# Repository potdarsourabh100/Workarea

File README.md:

# Workarea
My Own Personal Projects

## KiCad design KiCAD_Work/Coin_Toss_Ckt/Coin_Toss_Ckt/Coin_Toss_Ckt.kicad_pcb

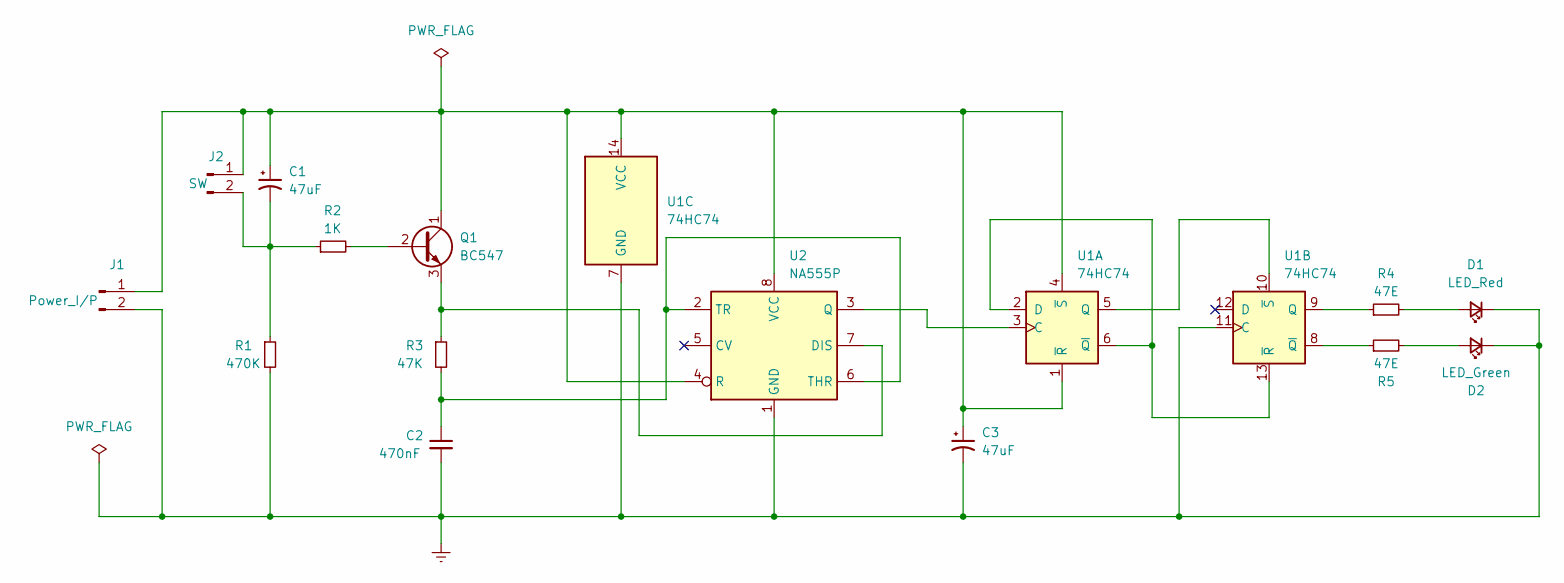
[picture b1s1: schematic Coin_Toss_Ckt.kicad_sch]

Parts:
C1, C3: 47uF; CP_Radial_D5.0mm_P2.50mm
C2: 470nF; CP_Radial_D5.0mm_P2.50mm
D1: LED_Red; LED_D3.0mm
D2: LED_Green; LED_D3.0mm
J1: Power_I/P; TerminalBlock_Phoenix_MPT-0,5-2-2.54_1x02_P2.54mm_Horizontal
J2: SW; PinHeader_1x02_P2.54mm_Vertical
Q1: BC547; TO-92_Inline
R1: 470K; R_Axial_DIN0207_L6.3mm_D2.5mm_P10.16mm_Horizontal
R2: 1K; R_Axial_DIN0207_L6.3mm_D2.5mm_P10.16mm_Horizontal
R3: 47K; R_Axial_DIN0207_L6.3mm_D2.5mm_P10.16mm_Horizontal
R4, R5: 47E; R_Axial_DIN0207_L6.3mm_D2.5mm_P10.16mm_Horizontal
U1: 74HC74; DIP-14_W7.62mm_Socket_LongPads
U2: NA555P; DIP-8_W7.62mm_Socket_LongPads

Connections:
Earth: C2.2, C3.2, D1.1 (K), D2.1 (K), J1.2, R1.2, U1.7 (GND), U1.11 (C), U2.1 (GND)
unnamed: C1.1, C3.1, J1.1, J2.1, Q1.1 (C), U1.1 (~R), U1.4 (~S), U1.14 (VCC), U2.4 (R), U2.8 (VCC)
unnamed: C1.2, J2.2, R1.1, R2.1
unnamed: C2.1, R3.2, U2.2 (TR), U2.6 (THR)
unnamed: D1.2 (A), R4.2
unnamed: D2.2 (A), R5.2
unnamed: Q1.2 (B), R2.2
unnamed: Q1.3 (E), R3.1, U2.7 (DIS)
unnamed: R4.1, U1.9 (Q)
unnamed: R5.1, U1.8 (~Q)
unnamed: U1.3 (C), U2.3 (Q)
unnamed: U1.5 (Q), U1.10 (~S)
unnamed: U1.2 (D), U1.6 (~Q), U1.13 (~R)

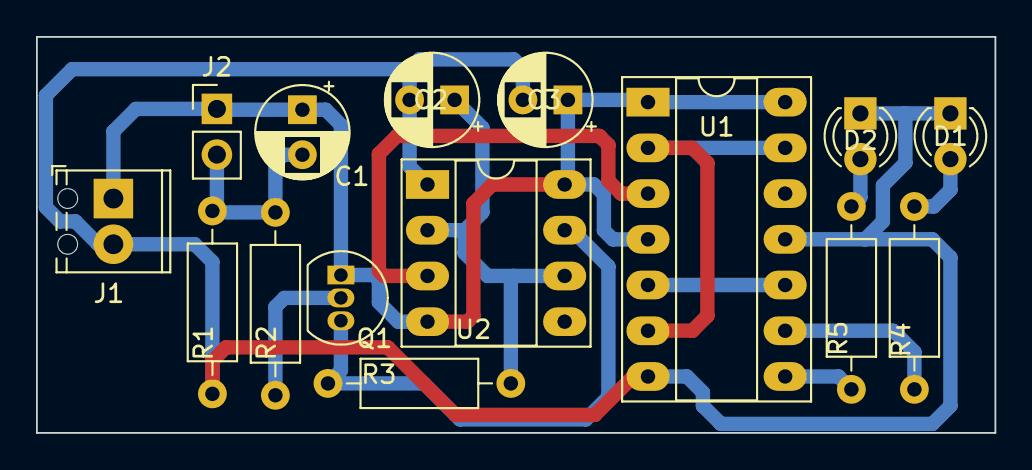
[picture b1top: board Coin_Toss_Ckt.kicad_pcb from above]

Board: 2 copper layers, 53.2 x 22.0 mm, 15 parts (0 on the bottom side), 13 nets.

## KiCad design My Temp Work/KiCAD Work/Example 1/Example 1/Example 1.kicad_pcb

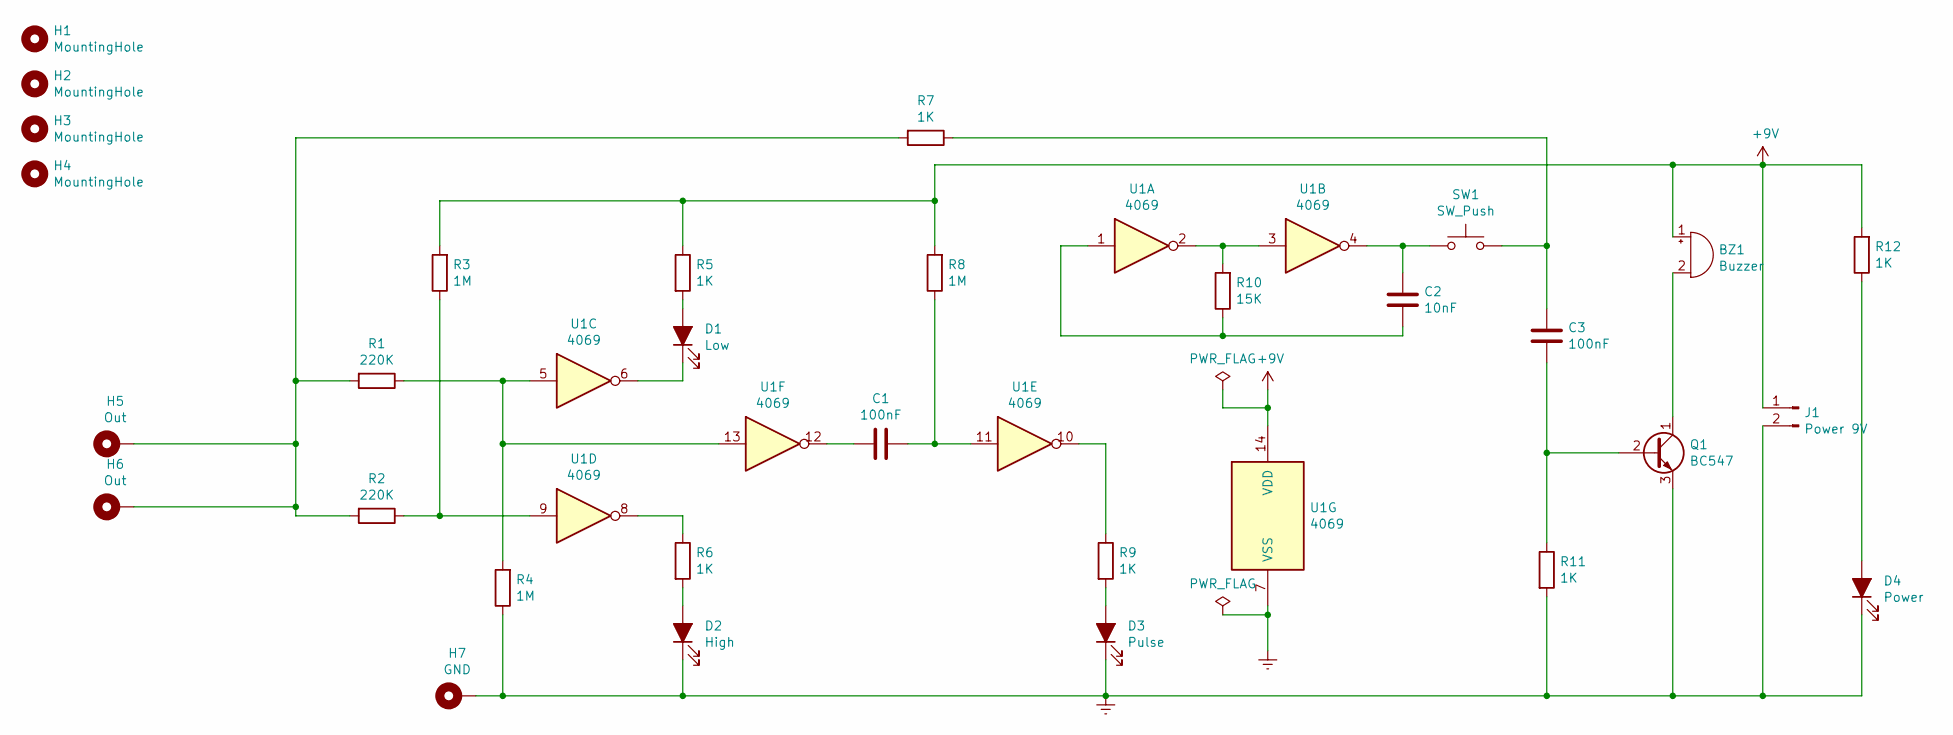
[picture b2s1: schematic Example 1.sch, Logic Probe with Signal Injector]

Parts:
BZ1: Buzzer; Buzzer_12x9.5RM7.6
C1, C3: 100nF; C_Disc_D6.0mm_W2.5mm_P5.00mm
C2: 10nF; C_Disc_D6.0mm_W2.5mm_P5.00mm
D1: Low; LED_D3.0mm
D2: High; LED_D3.0mm
D3: Pulse; LED_D3.0mm
D4: Power; LED_D3.0mm
H1, H2, H3, H4: MountingHole; MountingHole_3.2mm_M3
H5, H6: Out; MountingHole_2.5mm_Pad
H7: GND; MountingHole_2.5mm_Pad
J1: Power 9V; TerminalBlock_Phoenix_MKDS-1,5-2-5.08_1x02_P5.08mm_Horizont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
Q1: BC547; TO-92_Inline
R1, R2: 220K; R_Axial_DIN0207_L6.3mm_D2.5mm_P10.16mm_Horizontal
R3, R4, R8: 1M; R_Axial_DIN0207_L6.3mm_D2.5mm_P10.16mm_Horizontal
R5, R6, R7, R9, R11, R12: 1K; R_Axial_DIN0207_L6.3mm_D2.5mm_P10.16mm_Horizontal
R10: 15K; R_Axial_DIN0207_L6.3mm_D2.5mm_P10.16mm_Horizontal
SW1: SW_Push; SW_PUSH_6mm
U1: 4069; DIP-14_W7.62mm

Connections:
+9V: BZ1.1 (-), J1.1, R3.2, R5.1, R8.2, R12.2, U1.14 (VDD)
Earth: D2.1 (K), D3.1 (K), D4.1 (K), H7.1, J1.2, Q1.3 (E), R4.1, R11.2, U1.7 (VSS)
unnamed: BZ1.2 (+), Q1.1 (C)
unnamed: C1.1, R8.1, U1.11
unnamed: C1.2, U1.12
unnamed: C2.1, R10.1, U1.1
unnamed: C2.2, SW1.1, U1.4
unnamed: C3.1, Q1.2 (B), R11.1
unnamed: C3.2, R7.1, SW1.2
unnamed: D1.1 (K), U1.6
unnamed: D1.2 (A), R5.2
unnamed: D2.2 (A), R6.2
unnamed: D3.2 (A), R9.2
unnamed: D4.2 (A), R12.1
unnamed: H5.1, H6.1, R1.2, R2.2, R7.2
unnamed: R1.1, R4.2, U1.5, U1.13
unnamed: R2.1, R3.1, U1.9
unnamed: R6.1, U1.8
unnamed: R9.1, U1.10
unnamed: R10.2, U1.2, U1.3

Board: 2 copper layers, 31 parts (0 on the bottom side), 20 nets, no tracks yet.

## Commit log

2022-05-22 My First Commit
2022-05-22 My Second Commit
2022-05-23 Add files via upload
    Coin Toss PCB finish products
